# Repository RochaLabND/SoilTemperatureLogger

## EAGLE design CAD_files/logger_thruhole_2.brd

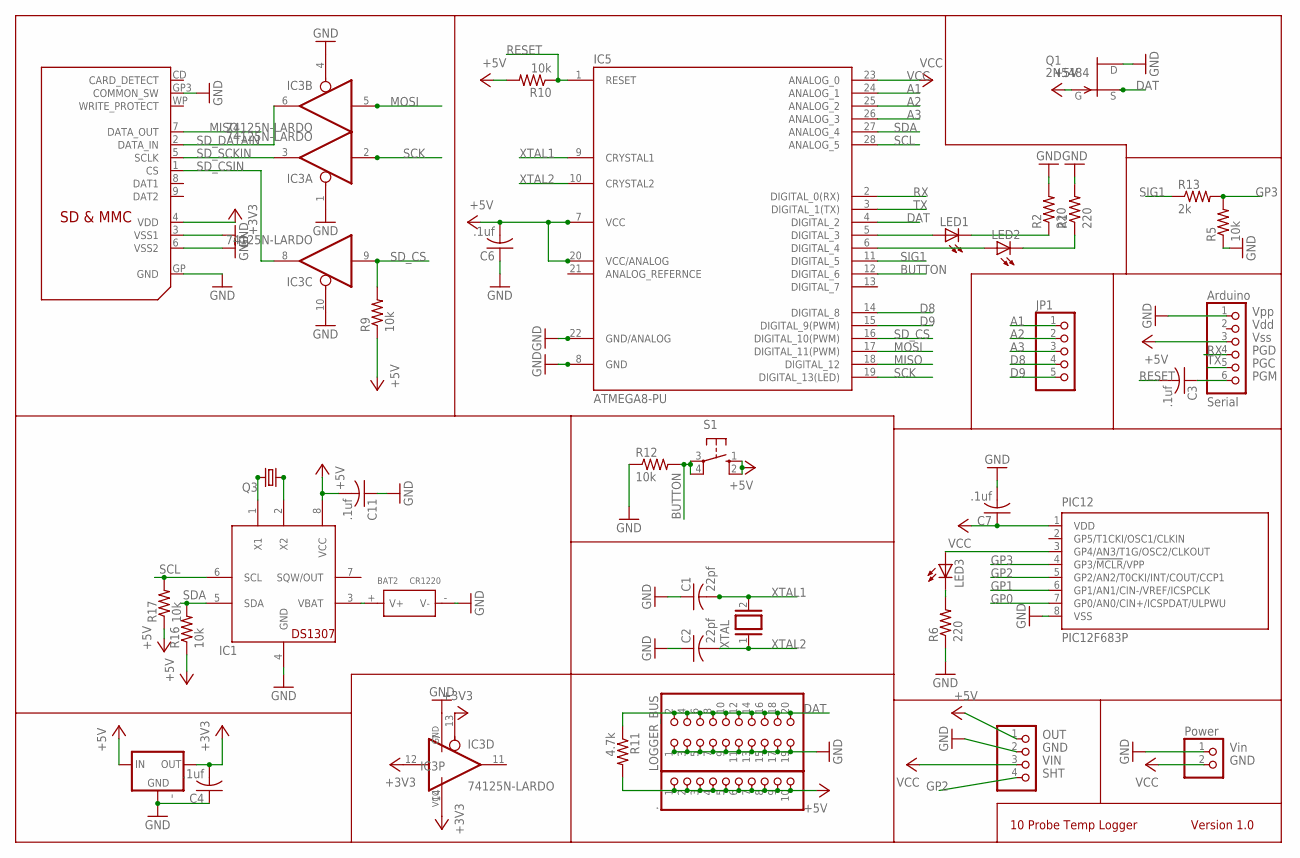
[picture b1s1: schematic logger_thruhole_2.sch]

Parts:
': MCP1700TRI; TO92
.: PINHD-1X10; 1X10
BAT2: CR1220; BAT2P-SMD-16.4-CR1220
C1, C2: 22pf; C025-025X050
C3, C4, C6, C7, C11: .1uf; C025-025X050
IC1: DS1307; DIL08
IC3: 74125N-LARDO; DIL14-LARDO
IC5: ATMEGA8-PU; DIL28-3
JP1: PINHD-1X5; 1X05
JP2: PINHD-1X6; 1X06
LED1, LED2, LED3: LEDLZR181; LZR181
LOGGER_BUS: PINHD-2X10; 2X10
PIC12: PIC12F683P; DIL8
POWER: PINHD-1X2; 1X02
Q1: 2N5484; TO92-
Q3: CRYSTALTC38H; TC38H
R1, R2, R6: 220; 0207/2V
R5, R9, R10, R12, R16, R17: 10k; 0207/2V
R11: 4.7k; 0207/2V
R13: 2k; 0207/2V
REG: PINHD-1X4; 1X04
S1: 10-XX; B3F-10XX
U$2: SDMMC06132; 06132
XTAL: XTAL/S; QS

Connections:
+3V3: '.3 (OUT), C4.2, IC3.12 (I), IC3.13 (OE), IC3.14 (VCC), U$2.4 (VDD)
+5V: '.2 (IN), ..1, ..2, ..3, ..4, ..5, ..6, ..7, ..8, ..9, ..10, C6.2, C11.2, IC1.8 (VCC), IC5.7 (VCC), IC5.20 (VCC/ANALOG), JP2.3, Q1.1 (G), R9.1, R10.2, R11.2, R16.1, R17.1, REG.1, S1.1 (S), S1.2 (S1)
A1: IC5.24 (ANALOG_1), JP1.1
A2: IC5.25 (ANALOG_2), JP1.2
A3: IC5.26 (ANALOG_3), JP1.3
BUTTON: IC5.12 (DIGITAL_6), R12.2, S1.3, S1.4 (P1)
D8: IC5.14 (DIGITAL_8), JP1.4
D9: IC5.15 (DIGITAL_9(PWM)), JP1.5
DAT: IC5.4 (DIGITAL_2), LOGGER_BUS.2, LOGGER_BUS.4, LOGGER_BUS.6, LOGGER_BUS.8, LOGGER_BUS.10, LOGGER_BUS.12, LOGGER_BUS.14, LOGGER_BUS.16, LOGGER_BUS.18, LOGGER_BUS.20, Q1.2 (S), R11.1
GND: '.1 (GND), BAT2.- (V-), C1.1, C2.1, C4.1, C6.1, C7.2, C11.1, IC1.4 (GND), IC3.1 (OE), IC3.4 (OE), IC3.7 (GND), IC3.10 (OE), IC5.8 (GND), IC5.22 (GND/ANALOG), JP2.1, LOGGER_BUS.1, LOGGER_BUS.3, LOGGER_BUS.5, LOGGER_BUS.7, LOGGER_BUS.9, LOGGER_BUS.11, LOGGER_BUS.13, LOGGER_BUS.15, LOGGER_BUS.17, LOGGER_BUS.19, PIC12.8 (VSS), POWER.1, Q1.3 (D), R1.2, R2.2, R5.1, R6.1, R12.1, REG.2, U$2.3 (VSS1), U$2.6 (VSS2), U$2.GP (GND), U$2.GP3 (COMMON_SW)
GP0: PIC12.7 (GP0/AN0/CIN+/ICSPDAT/ULPWU)
GP1: PIC12.6 (GP1/AN1/CIN-/VREF/ICSPCLK)
GP2: PIC12.5 (GP2/AN2/T0CKI/INT/COUT/CCP1), REG.4
GP3: PIC12.4 (GP3/!MCLR!/VPP), R5.2, R13.2
MISO: IC5.18 (DIGITAL_12), U$2.7 (DATA_OUT)
MOSI: IC3.5 (I), IC5.17 (DIGITAL_11(PWM))
unnamed: IC5.5 (DIGITAL_3), LED1.A
unnamed: BAT2.+ (V+), IC1.3 (VBAT)
unnamed: IC5.6 (DIGITAL_4), LED2.A
unnamed: LED3.A, PIC12.3 (GP4/AN3/T1G/OSC2/CLKOUT)
unnamed: IC1.1 (X1), Q3.2
unnamed: LED1.K (C), R2.1
unnamed: IC1.2 (X2), Q3.1
unnamed: LED2.K (C), R1.1
unnamed: LED3.K (C), R6.2
unnamed: C3.1, JP2.6
RESET: C3.2, IC5.1 (RESET), R10.1
RX: IC5.2 (DIGITAL_0(RX)), JP2.4
SCK: IC3.2 (I), IC5.19 (DIGITAL_13(LED))
SCL: IC1.6 (SCL), IC5.28 (ANALOG_5), R17.2
SDA: IC1.5 (SDA), IC5.27 (ANALOG_4), R16.2
SD_CS: IC3.9 (I), IC5.16 (DIGITAL_10(PWM)), R9.2
SD_CSIN: IC3.8 (O), U$2.1 (CS)
SD_DATAIN: IC3.6 (O), U$2.2 (DATA_IN)
SD_SCKIN: IC3.3 (O), U$2.5 (SCLK)
SIG1: IC5.11 (DIGITAL_5), R13.1
TX: IC5.3 (DIGITAL_1(TX)), JP2.5
VCC: C7.1, IC5.23 (ANALOG_0), PIC12.1 (VDD), POWER.2, REG.3
XTAL1: C1.2, IC5.9 (CRYSTAL1), XTAL.2
XTAL2: C2.2, IC5.10 (CRYSTAL2), XTAL.1

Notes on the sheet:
10 Probe Temp Logger
Version 1.0

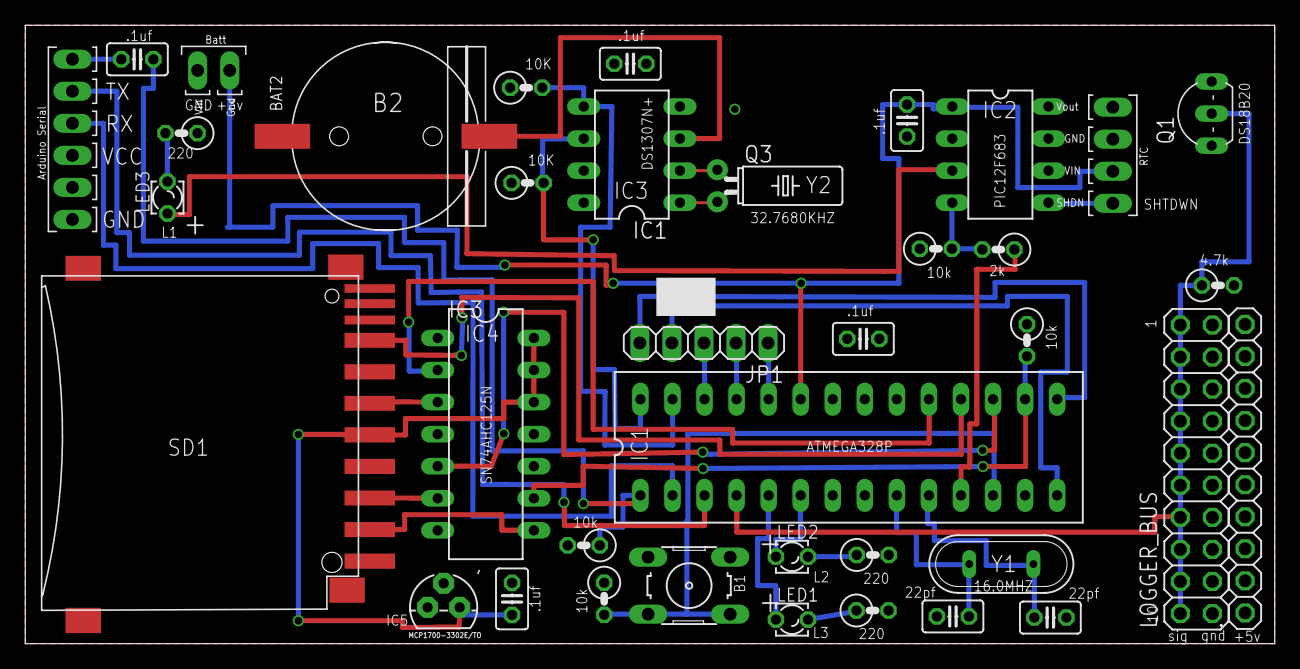
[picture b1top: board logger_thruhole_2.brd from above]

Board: 2 copper layers, 99.0 x 49.0 mm, 38 parts (0 on the bottom side), 38 nets.

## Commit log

2021-10-21 Add files via upload
    Added a sample of soil temperature data collected in the field using the DIY soil temperature logger.
    -Ian
2021-11-12 Added CAD_files
2021-12-14 added instructional videos
2022-10-23 Document and code additions
    Changes
    1. Added troubleshooting tips document and useful manual.
    2. Added two untested versions of the data logger code.
2023-01-12 added a list of substitute parts
